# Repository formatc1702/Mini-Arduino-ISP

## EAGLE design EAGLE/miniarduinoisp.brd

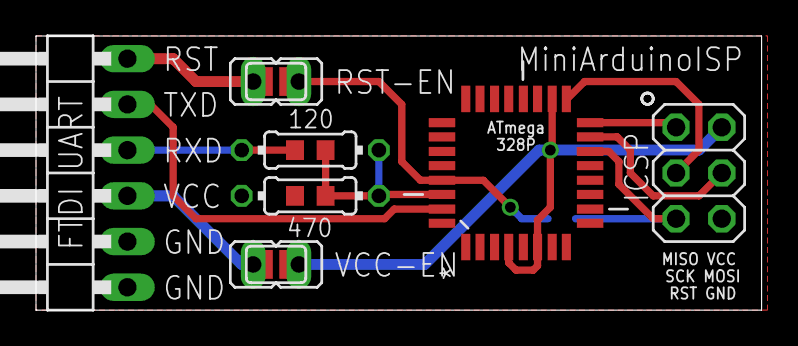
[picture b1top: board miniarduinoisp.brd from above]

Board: 2 copper layers, 40.3 x 15.2 mm, 12 parts (1 on the bottom side), 12 nets.

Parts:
JP-ICSP: 2X03
JP-RST-EN: JP1
JP-UART: 1X06/90
JP-VCC-EN: JP1
R1: 120; 0204/7
R1SMD: 120; R0603
R2: 470; 0204/7
R2SMD: 470; R0603
SJ-PROG: SJ
SJ-RST-EN: SJ
SJ-VCC-EN: SJ
U1: ATMEGA328P-AU; QFP80P900X900X120-32N

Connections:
GND: JP-ICSP.6, JP-UART.1, JP-UART.2, R2.1, R2SMD.1, U1.3, U1.5, U1.21
MISO: JP-ICSP.1, U1.16
MOSI: JP-ICSP.4, U1.15
RST: JP-ICSP.5, SJ-PROG.1, U1.14
SCK: JP-ICSP.3, U1.17
UART-DTR: JP-RST-EN.2, JP-UART.6, SJ-RST-EN.2
UART-RX/UC-TX: JP-UART.5, U1.31
UART-TX: JP-UART.4, R1.2, R1SMD.2
UC-RESET: JP-RST-EN.1, SJ-PROG.2, SJ-RST-EN.1, U1.29
UC-RX: R1.1, R1SMD.1, R2.2, R2SMD.2, U1.30
VCC: JP-ICSP.2, JP-VCC-EN.2, SJ-VCC-EN.2, U1.4, U1.6, U1.18
VCC-UART: JP-UART.3, JP-VCC-EN.1, SJ-VCC-EN.1

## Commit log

2014-12-03 Initial upload
2014-12-03 Added schematic PDF
2016-10-15 Reorder files
